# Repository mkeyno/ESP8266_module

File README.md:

# small footprint ESP8266 & ESP32 module for industrial application 
2 x 8 pins Efor SP8266   
4 x 7 pins for ESP32

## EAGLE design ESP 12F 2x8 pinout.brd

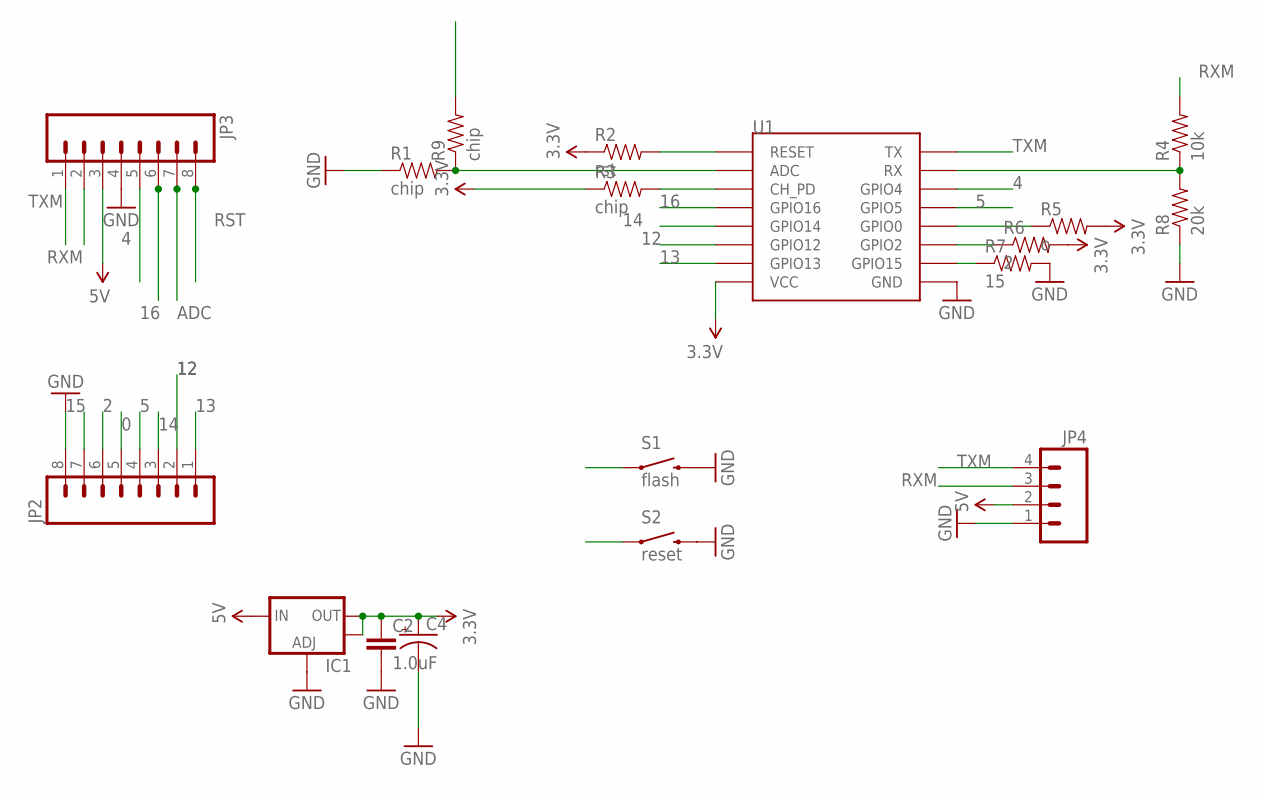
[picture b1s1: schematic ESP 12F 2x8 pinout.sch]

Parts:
C2: 1.0uF; 1206
C4: 47UF-50V-20%(ELECT); PANASONIC_D
IC1: V_REG_LM1117SOT223; SOT223
JP2, JP3: M08; 1X08_ROUND
JP4: M04PTH; 1X04
R1, R3, R9: chip; 0805
R2: rst; 0805
R4: 10k; 0805
R5: o; 0805
R6: 2; 0805
R7: 15; 0805
R8: 20k; 0805
S1: flash; TACTILE-SWITCH-1101NE
S2: reset; TACTILE-SWITCH-1101NE
U1: ESP12SMD; ESP12-SMD

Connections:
0: JP2.5, R5.1, S1.1, U1.GPIO0
2: JP2.6, R6.1, U1.GPIO2
3.3V: C2.1, C4.+, IC1.2 (OUT), IC1.4 (OUT), R2.1, R3.1, R5.2, R6.2, U1.VCC
4: JP3.5, U1.GPIO4
5: JP2.4, U1.GPIO5
5V: IC1.3 (IN), JP3.3, JP4.2
12: JP2.2, U1.GPIO12
13: JP2.1, U1.GPIO13
14: JP2.3, U1.GPIO14
15: JP2.7, R7.1, U1.GPIO15
16: JP3.6, U1.GPIO16
ADC: JP3.7, R9.2
ADCM: R1.2, R9.1, U1.ADC
CH_PD: R3.2, U1.CH_PD
GND: C2.2, C4.-, IC1.1 (ADJ), JP2.8, JP3.4, JP4.1, R1.1, R7.2, R8.1, S1.2, S2.2, U1.GND
unnamed: R4.1, R8.2, U1.RXD0 (RX)
RST: JP3.8, R2.2, S2.1, U1.RESET
RXM: JP3.2, JP4.3, R4.2
TXM: JP3.1, JP4.4, U1.TXD0 (TX)

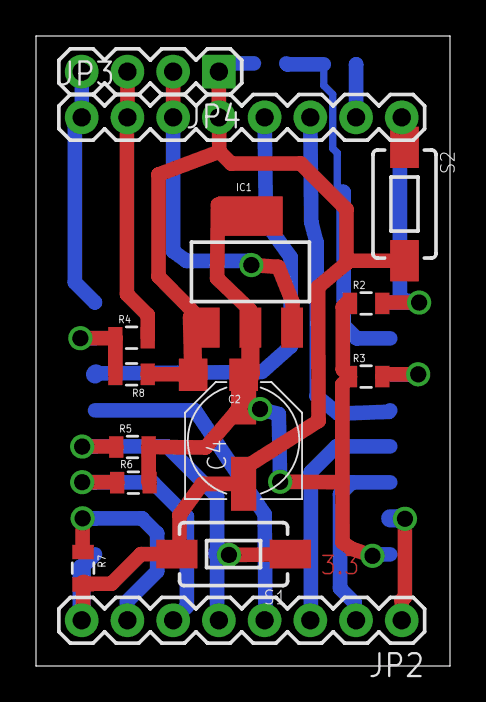
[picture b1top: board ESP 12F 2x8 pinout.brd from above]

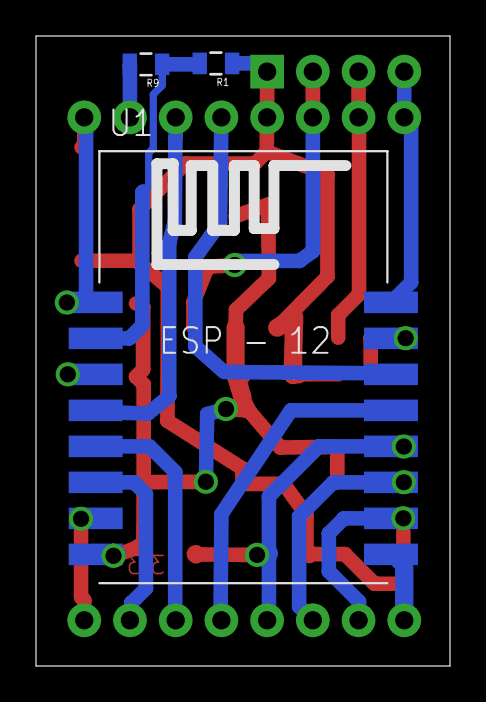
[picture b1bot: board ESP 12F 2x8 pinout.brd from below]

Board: 2 copper layers, 23.0 x 35.0 mm, 18 parts (3 on the bottom side), 19 nets.

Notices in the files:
parts and their libraries:
SparkFun-Capacitors: Licensing: Creative Commons ShareAlike 4.0 International - https://creativecommons.org/licenses/by-sa/4.0
